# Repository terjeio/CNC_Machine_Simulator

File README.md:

## CNC Machine Simulator

#### *** PRELIMINARY ***

First batch of boards \(for final design verification\) to be ordered soon.

**NOTE:** design files are in [KiCad 5](http://www.kicad.org/) format!

**Features:**

* Board based on a Cypress CY8CKIT-059 devkit \(PSoC 5\).

* OLED display showing motor pulse counts and status information.

* 3.3v or 5v signalling.

* Step, dir and enable inputs for up to four motors.

* Four limit pins outputs with configurable trigger count can be used to simulate auto-squaring.

* Signal outputs for reset/E-stop, safety door, feed hold, cycle start and aux input 0 - 2. Aux 0 and 1 can be used to generate spindle encoder signals.

* Device control inputs for spindle on, spindle dir, flood, mist aux output 0 and 1.

* 5v I2C port.

* 5v UART port - can be used to simulate VFD.

* Analog output for simulating arc voltage.

* PWM/analog input for spindle RPM control.

---

2021-10-21

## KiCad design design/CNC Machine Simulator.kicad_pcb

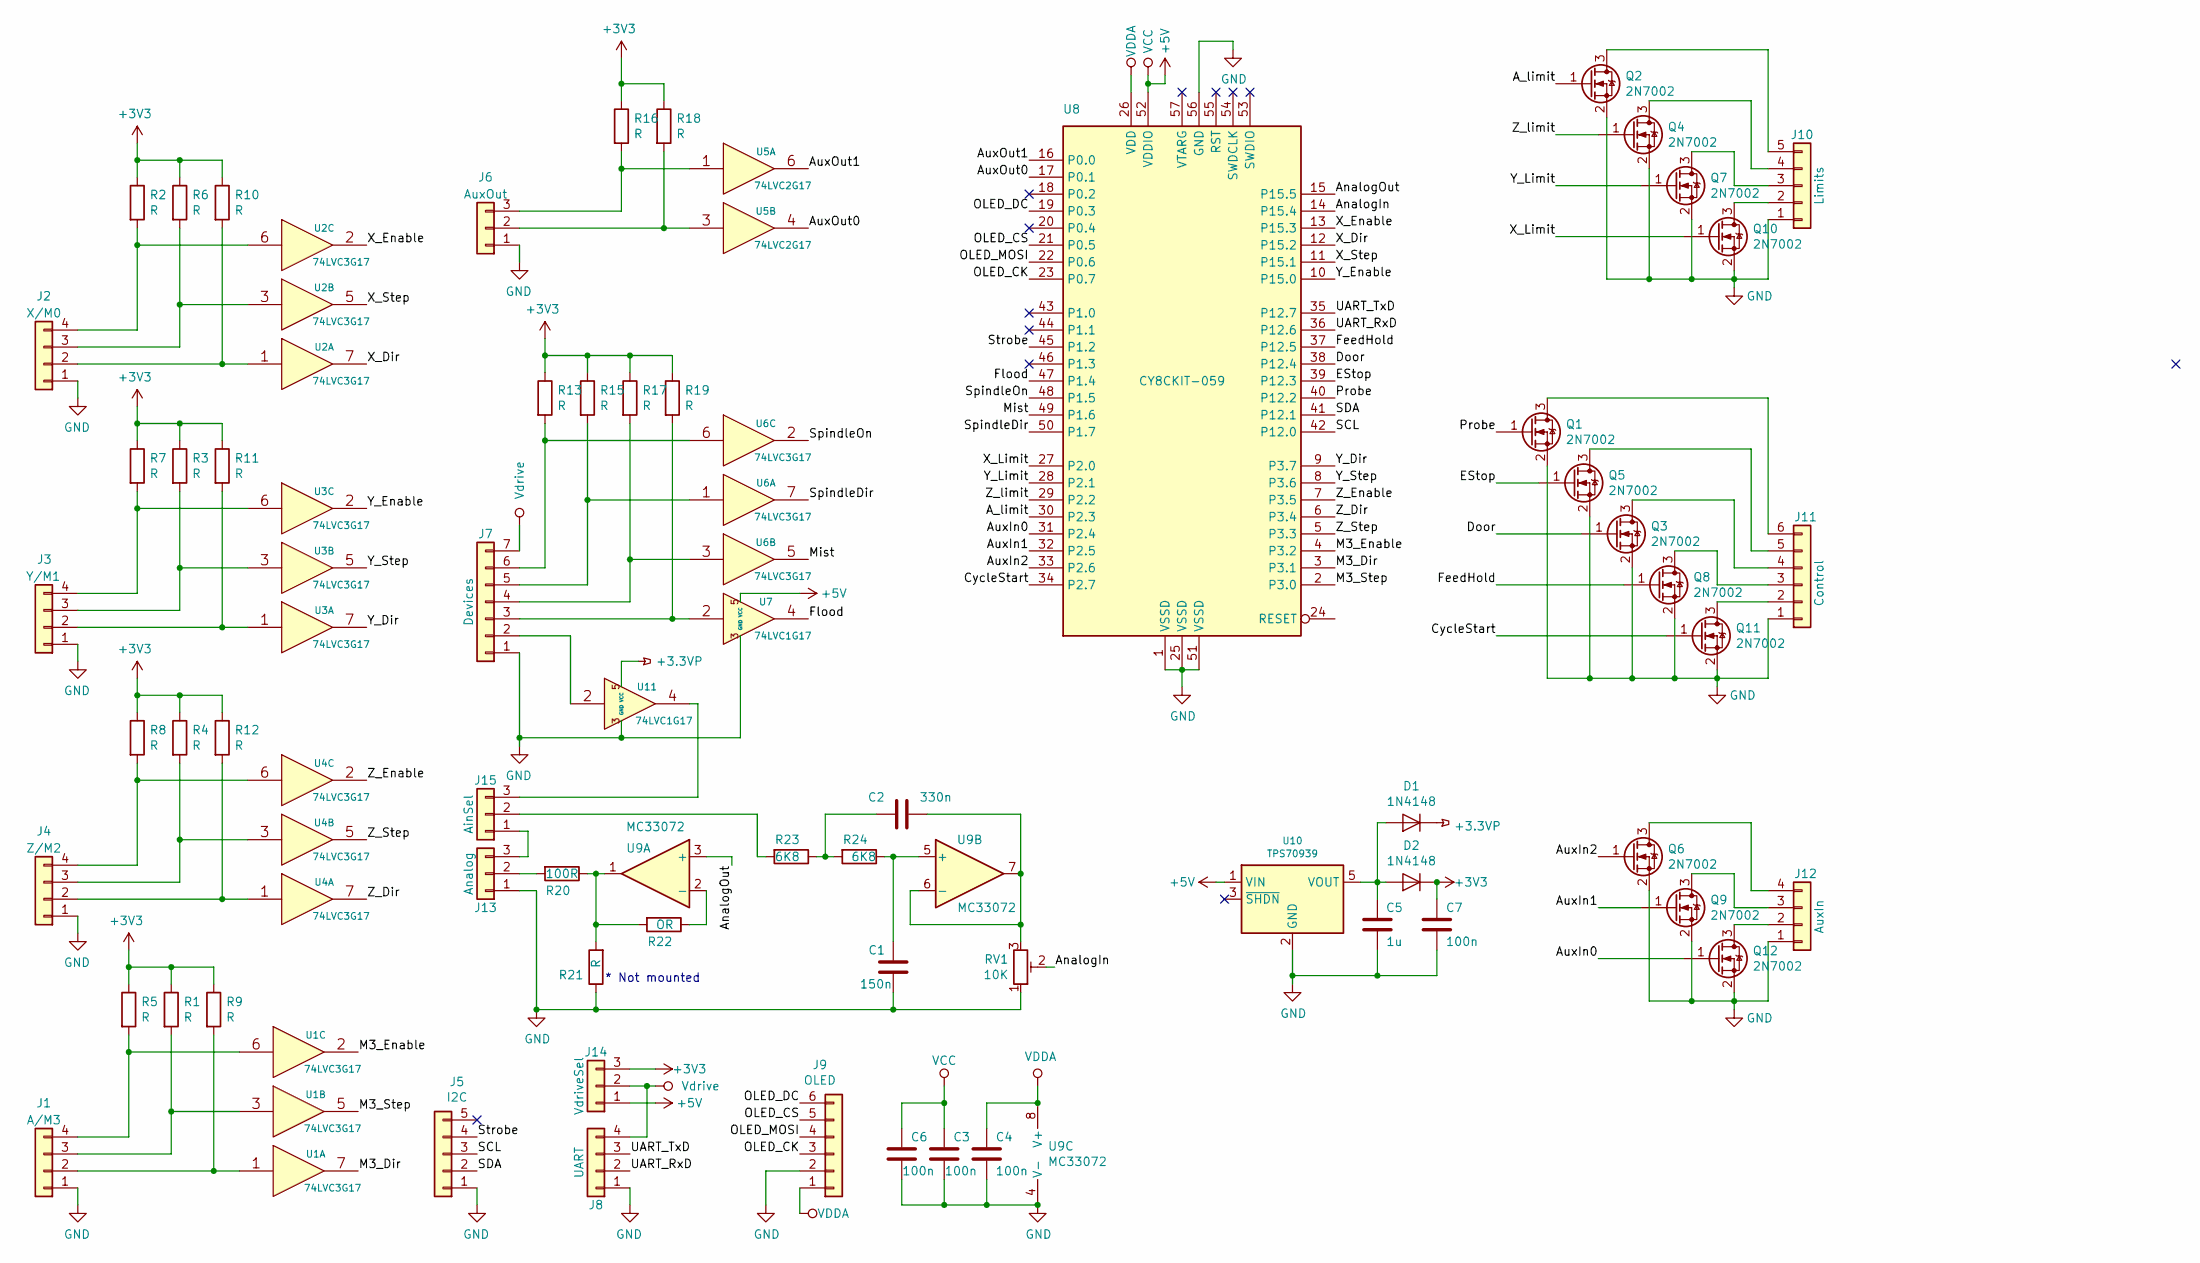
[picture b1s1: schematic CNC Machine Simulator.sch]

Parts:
C1: 150n; C_0805_2012Metric
C2: 330n; C_0805_2012Metric
C3, C4, C6, C7: 100n; C_0805_2012Metric
C5: 1u; C_0805_2012Metric
D1, D2: 1N4148; D_SOD-123
J1: A/M3; PinHeader_1x04_P2.54mm_Vertical
J2: X/M0; PinHeader_1x04_P2.54mm_Vertical
J3: Y/M1; PinHeader_1x04_P2.54mm_Vertical
J4: Z/M2; PinHeader_1x04_P2.54mm_Vertical
J5: I2C; PinHeader_1x05_P2.54mm_Vertical
J6: AuxOut; PinHeader_1x03_P2.54mm_Vertical
J7: Devices; PinHeader_1x07_P2.54mm_Vertical
J8: UART; PinHeader_1x04_P2.54mm_Vertical
J9: OLED; PinHeader_1x06_P2.54mm_Vertical
J10: Limits; PinHeader_1x05_P2.54mm_Vertical
J11: Control; PinHeader_1x06_P2.54mm_Vertical
J12: AuxIn; PinHeader_1x04_P2.54mm_Vertical
J13: Analog; PinHeader_1x03_P2.54mm_Vertical
J14: VdriveSel; PinHeader_1x03_P2.54mm_Vertical
J15: AinSel; PinHeader_1x03_P2.54mm_Vertical
Q1, Q2, Q3, Q4, Q5, Q6, Q7, Q8, Q9, Q10, Q11, Q12: 2N7002; SOT-23
R1, R2, R3, R4, R5, R6, R7, R8, R9, R10, R11, R12, R13, R15, R16, R17, R18, R19, R21: R; R_0805_2012Metric
R20: 100R; R_0805_2012Metric
R22: OR; R_0805_2012Metric
R23, R24: 6K8; R_0805_2012Metric
RV1: 10K; Potentiometer_Bourns_3296W_Vertical
U1, U2, U3, U4, U6: 74LVC3G17; SSOP-8_2.95x2.8mm_P0.65mm
U5: 74LVC2G17; SOT-23-6
U7, U11: 74LVC1G17; SOT-353_SC-70-5
U8: CY8CKIT-059; CY8CKIT_059
U9: MC33072; SOIC-8_3.9x4.9mm_P1.27mm
U10: TPS70939; SOT-23-5

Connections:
+3.3VP: D1.1 (K), U11.5 (VCC)
+3V3: C7.1, D2.1 (K), J14.3, R1.1, R2.1, R3.1, R4.1, R5.1, R6.1, R7.1, R8.1, R9.1, R10.1, R11.1, R12.1, R13.1, R15.1, R16.1, R17.1, R18.1, R19.1
+5V: C3.1, C6.1, J14.1, U1.8 (VCC), U2.8 (VCC), U3.8 (VCC), U4.8 (VCC), U5.5 (VCC), U6.8 (VCC), U7.5 (VCC), U8.52 (VDDIO), U10.1 (VIN)
/A_limit: Q2.1 (G), U8.30 (P2.3)
/AnalogIn: RV1.2, U8.14 (P15.4)
/AnalogOut: U8.15 (P15.5), U9.3 (+)
/AuxIn0: Q12.1 (G), U8.31 (P2.4)
/AuxIn1: Q9.1 (G), U8.32 (P2.5)
/AuxIn2: Q6.1 (G), U8.33 (P2.6)
/AuxOut0: U5.4, U8.17 (P0.1)
/AuxOut1: U5.6, U8.16 (P0.0)
/CycleStart: Q11.1 (G), U8.34 (P2.7)
/Door: Q3.1 (G), U8.38 (P12.4)
/EStop: Q5.1 (G), U8.39 (P12.3)
/FeedHold: Q8.1 (G), U8.37 (P12.5)
/Flood: U7.4, U8.47 (P1.4)
/M3_Dir: U1.7, U8.3 (P3.1)
/M3_Enable: U1.2, U8.4 (P3.2)
/M3_Step: U1.5, U8.2 (P3.0)
/Mist: U6.5, U8.49 (P1.6)
/OLED_CK: J9.3, U8.23 (P0.7)
/OLED_CS: J9.5, U8.21 (P0.5)
/OLED_DC: J9.6, U8.19 (P0.3)
/OLED_MOSI: J9.4, U8.22 (P0.6)
/Probe: Q1.1 (G), U8.40 (P12.2)
/SCL: J5.3, U8.42 (P12.0)
/SDA: J5.2, U8.41 (P12.1)
/SpindleDir: U6.7, U8.50 (P1.7)
/SpindleOn: U6.2, U8.48 (P1.5)
/Strobe: J5.4, U8.45 (P1.2)
/UART_RxD: J8.2, U8.36 (P12.6)
/UART_TxD: J8.3, U8.35 (P12.7)
/X_Dir: U2.7, U8.12 (P15.2)
/X_Enable: U2.2, U8.13 (P15.3)
/X_Limit: Q10.1 (G), U8.27 (P2.0)
/X_Step: U2.5, U8.11 (P15.1)
/Y_Dir: U3.7, U8.9 (P3.7)
/Y_Enable: U3.2, U8.10 (P15.0)
/Y_Limit: Q7.1 (G), U8.28 (P2.1)
/Y_Step: U3.5, U8.8 (P3.6)
/Z_Dir: U4.7, U8.6 (P3.4)
/Z_Enable: U4.2, U8.7 (P3.5)
/Z_Step: U4.5, U8.5 (P3.3)
/Z_limit: Q4.1 (G), U8.29 (P2.2)
GND: C1.2, C3.2, C4.2, C5.2, C6.2, C7.2, J1.1, J2.1, J3.1, J4.1, J5.1, J6.1, J7.1, J8.1, J9.2, J10.1, J11.1, J12.1, J13.1, Q1.2 (S), Q2.2 (S), Q3.2 (S), Q4.2 (S), Q5.2 (S), Q6.2 (S), Q7.2 (S), Q8.2 (S), Q9.2 (S), Q10.2 (S), Q11.2 (S), Q12.2 (S), R21.1, RV1.1, U1.4 (GND), U2.4 (GND), U3.4 (GND), U4.4 (GND), U5.2 (GND), U6.4 (GND), U7.3 (GND), U8.1 (VSSD), U8.25 (VSSD), U8.51 (VSSD), U8.56 (GND), U9.4 (V-), U10.2 (GND), U11.3 (GND)
unnamed: C1.1, R24.1, U9.5 (+)
unnamed: C2.1, R23.1, R24.2
unnamed: C2.2, RV1.3, U9.6 (-), U9.7
unnamed: C5.1, D1.2 (A), D2.2 (A), U10.5 (VOUT)
unnamed: J1.2, R9.2, U1.1
unnamed: J1.3, R1.2, U1.3
unnamed: J1.4, R5.2, U1.6
unnamed: J2.2, R10.2, U2.1
unnamed: J2.3, R6.2, U2.3
unnamed: J2.4, R2.2, U2.6
unnamed: J3.2, R11.2, U3.1
unnamed: J3.3, R3.2, U3.3
unnamed: J3.4, R7.2, U3.6
unnamed: J4.2, R12.2, U4.1
unnamed: J4.3, R4.2, U4.3
unnamed: J4.4, R8.2, U4.6
unnamed: J6.2, R18.2, U5.3
unnamed: J6.3, R16.2, U5.1
unnamed: J7.2, U11.2
unnamed: J7.3, R19.2, U7.2
unnamed: J7.4, R17.2, U6.3
unnamed: J7.5, R15.2, U6.1
unnamed: J7.6, R13.2, U6.6
unnamed: J10.2, Q10.3 (D)
unnamed: J10.3, Q7.3 (D)
unnamed: J10.4, Q4.3 (D)
unnamed: J10.5, Q2.3 (D)
unnamed: J11.2, Q11.3 (D)
unnamed: J11.3, Q8.3 (D)
unnamed: J11.4, Q3.3 (D)
unnamed: J11.5, Q5.3 (D)
unnamed: J11.6, Q1.3 (D)
unnamed: J12.2, Q12.3 (D)
unnamed: J12.3, Q9.3 (D)
unnamed: J12.4, Q6.3 (D)
unnamed: J13.2, R20.2
unnamed: J13.3, J15.1
unnamed: J15.2, R23.2
unnamed: J15.3, U11.4
unnamed: R20.1, R21.2, R22.2, U9.1
unnamed: R22.1, U9.2 (-)
VDDA: C4.1, J9.1, U8.26 (VDD), U9.8 (V+)
Vdrive: J7.7, J8.4, J14.2

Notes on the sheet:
* Not mounted

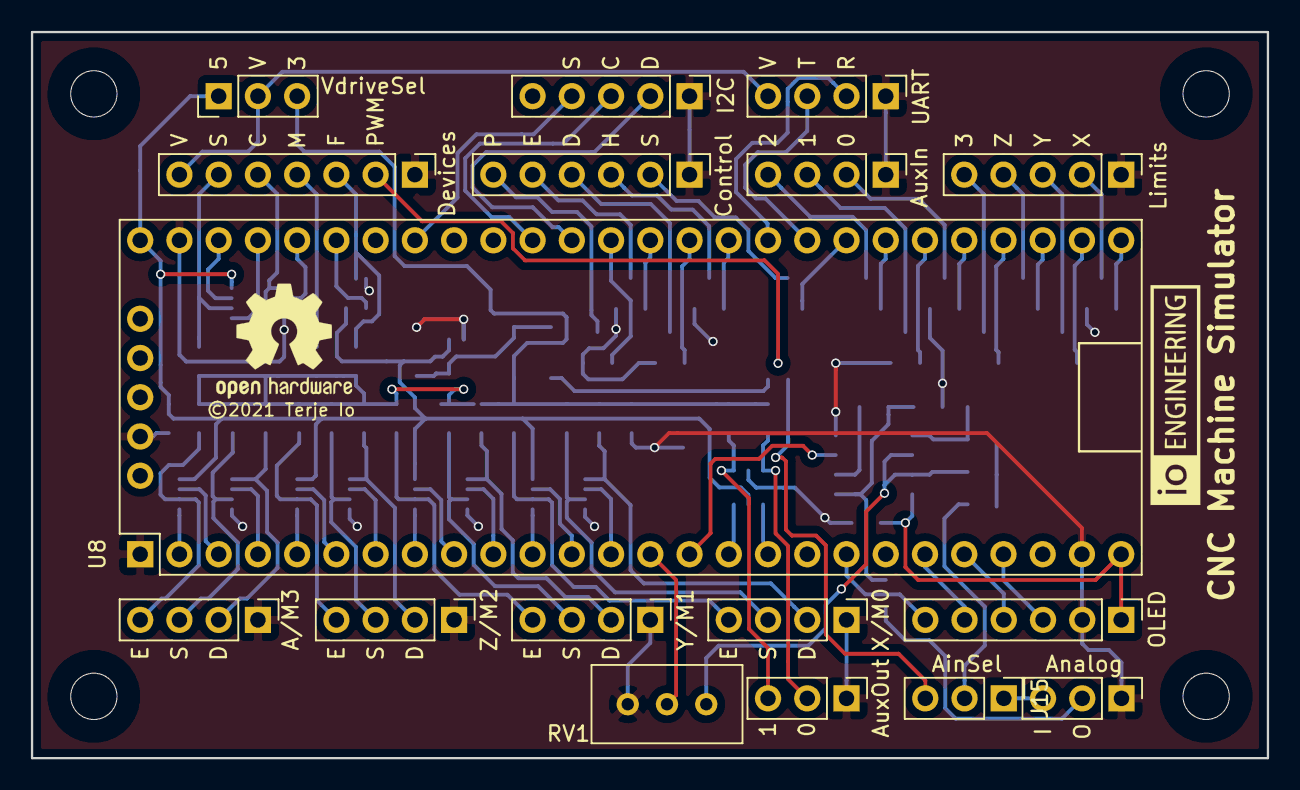
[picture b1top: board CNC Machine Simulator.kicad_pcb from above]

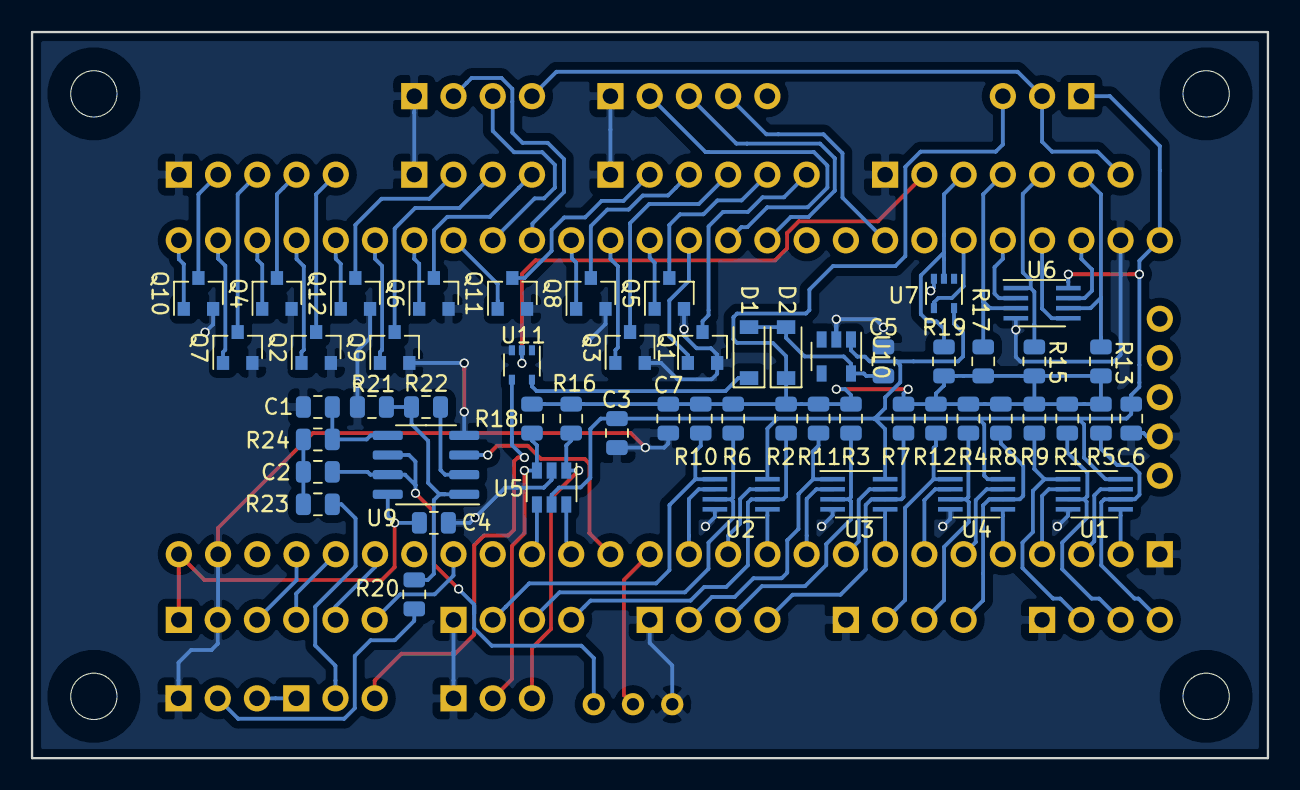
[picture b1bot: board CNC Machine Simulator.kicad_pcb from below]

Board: 2 copper layers, 80.0 x 47.0 mm, 71 parts (54 on the bottom side), 88 nets.

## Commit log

2021-10-21 Updated kicad link

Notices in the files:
design/CNC Machine Simulator.kicad_pcb:
©2021 Terje Io
